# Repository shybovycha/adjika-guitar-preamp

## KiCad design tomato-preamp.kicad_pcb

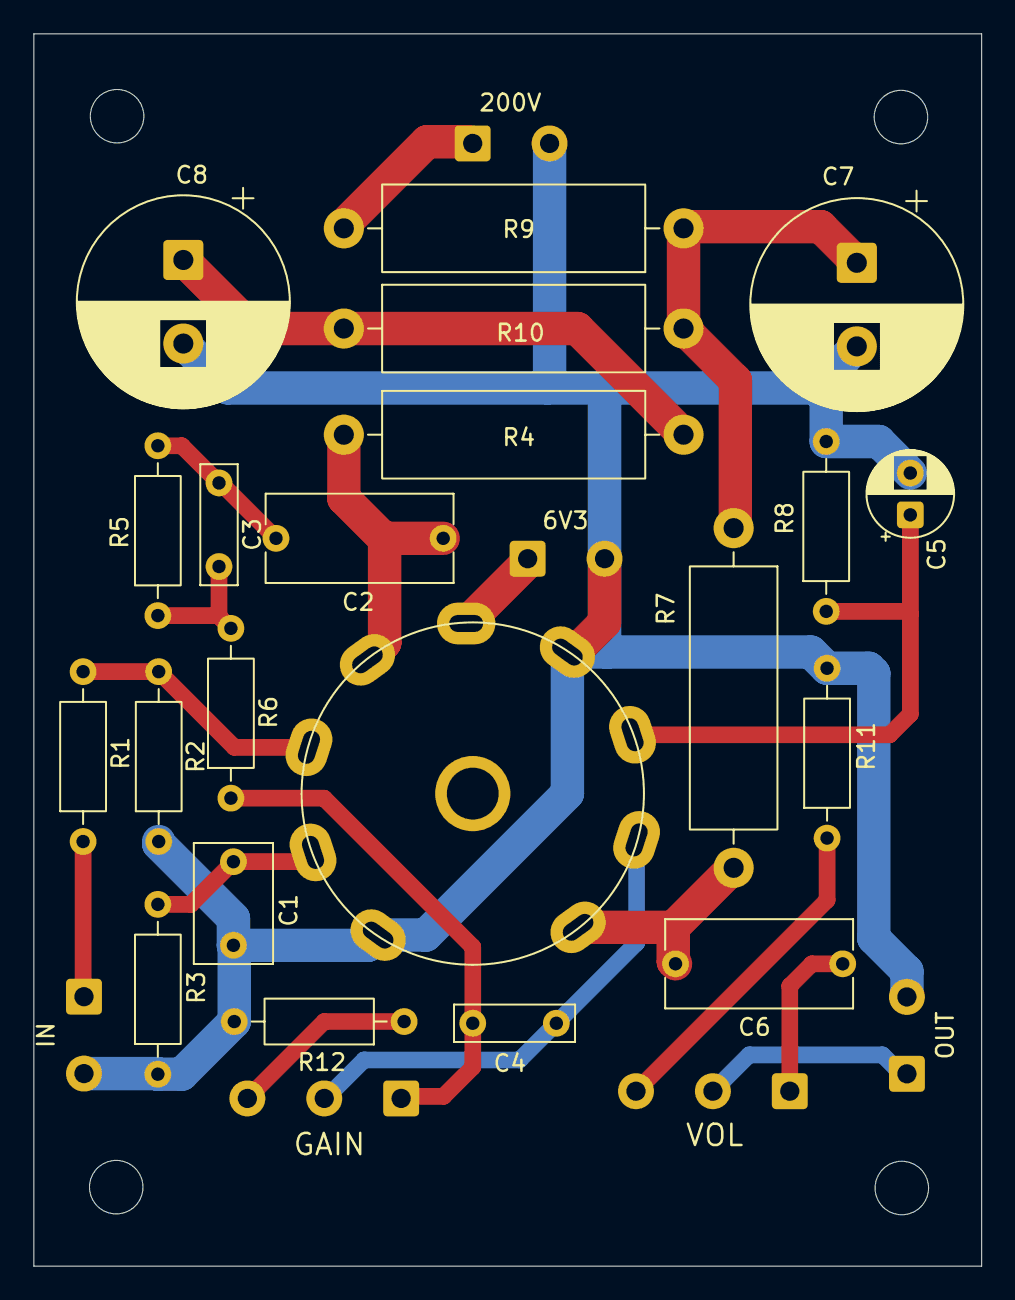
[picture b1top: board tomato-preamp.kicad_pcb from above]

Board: 2 copper layers, 56.7 x 73.7 mm, 31 parts (0 on the bottom side), 19 nets.

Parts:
C1: 470n 100V; C_Rect_L7.0mm_W4.5mm_P5.00mm
C2: 47n 400V; C_Rect_L11.0mm_W5.1mm_P10.00mm_MKT
C3, C4: 470p 400V; C_Rect_L7.0mm_W2.0mm_P5.00mm
C5: 2.2u 25V; CP_Radial_D5.0mm_P2.50mm
C6: 22n 400V; C_Rect_L11.0mm_W5.1mm_P10.00mm_MKT
C7, C8: 22u 400V; CP_Radial_D12.5mm_P5.00mm
H1, H2, H3, H4: MountingHole_Pad; MountingHole_3.2mm_M3
J3: 200V; SolderWire-0.5sqmm_1x02_P4.6mm_D0.9mm_OD2.1mm
J4: 6V3; SolderWire-0.5sqmm_1x02_P4.6mm_D0.9mm_OD2.1mm
J5: IN; SolderWire-0.5sqmm_1x02_P4.6mm_D0.9mm_OD2.1mm
J6: OUT; SolderWire-0.5sqmm_1x02_P4.6mm_D0.9mm_OD2.1mm
R1: 68k; R_Axial_DIN0207_L6.3mm_D2.5mm_P10.16mm_Horizontal
R2: 1M; R_Axial_DIN0207_L6.3mm_D2.5mm_P10.16mm_Horizontal
R3: 2.2k; R_Axial_DIN0207_L6.3mm_D2.5mm_P10.16mm_Horizontal
R4, R7: 32k 2W; R_Axial_DIN0516_L15.5mm_D5.0mm_P20.32mm_Horizontal
R5, R6: 470k; R_Axial_DIN0207_L6.3mm_D2.5mm_P10.16mm_Horizontal
R8: 1k; R_Axial_DIN0207_L6.3mm_D2.5mm_P10.16mm_Horizontal
R9, R10: 1K 2W; R_Axial_DIN0516_L15.5mm_D5.0mm_P20.32mm_Horizontal
R11, R12: 1K; R_Axial_DIN0207_L6.3mm_D2.5mm_P10.16mm_Horizontal
RV1: 1M; SolderWire-0.5sqmm_1x03_P4.6mm_D0.9mm_OD2.1mm
RV2: 100k; SolderWire-0.5sqmm_1x03_P4.6mm_D0.9mm_OD2.1mm
U1: 6N2P; Valve_6N2P-3

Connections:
GND: C1.2, C5.2, C7.2, C8.2, J3.2, J4.2, J5.2, J6.2, R2.1, R3.1, R8.2, R11.2, R12.2, U1.4 (H1), U1.9 (S)
unnamed: C2.2, C3.1, R5.2
unnamed: C3.2, R5.1, R6.2
unnamed: C4.1, R6.1, RV1.1
unnamed: C6.2, RV2.1
unnamed: C7.1, R7.1, R9.1, R10.2
unnamed: C8.1, R4.2, R10.1
unnamed: J3.1, R9.2
unnamed: J4.1, U1.5 (H1)
unnamed: J5.1, R1.1
unnamed: J6.1, RV2.2
unnamed: R11.1, RV2.3
unnamed: R12.1, RV1.3
unnamed: C2.1, R4.1, U1.6 (A)
unnamed: R1.2, R2.2, U1.7 (G)
unnamed: C1.1, R3.2, U1.8 (K)
unnamed: C6.1, R7.2, U1.1 (A)
unnamed: C4.2, RV1.2, U1.2 (G)
unnamed: C5.1, R8.1, U1.3 (K)

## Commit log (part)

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2026-02-13 Initial design
2026-02-13 single-layer version
2026-02-13 moving potentiometers to the equidistant places
2026-02-13 shorten the traces
2026-02-13 a slightly refined board
2026-02-13 intermittent
2026-02-13 update CBB capacitors footprints
2026-02-26 Update footprints
2026-03-02 Add modifications to the schematic
2026-03-02 Add docs
2026-06-03 Temp
2026-06-03 Rewire
2026-06-25 Reorganize layout
2026-06-25 Beautiful layout
2026-06-26 Layout with spacing for knobs
